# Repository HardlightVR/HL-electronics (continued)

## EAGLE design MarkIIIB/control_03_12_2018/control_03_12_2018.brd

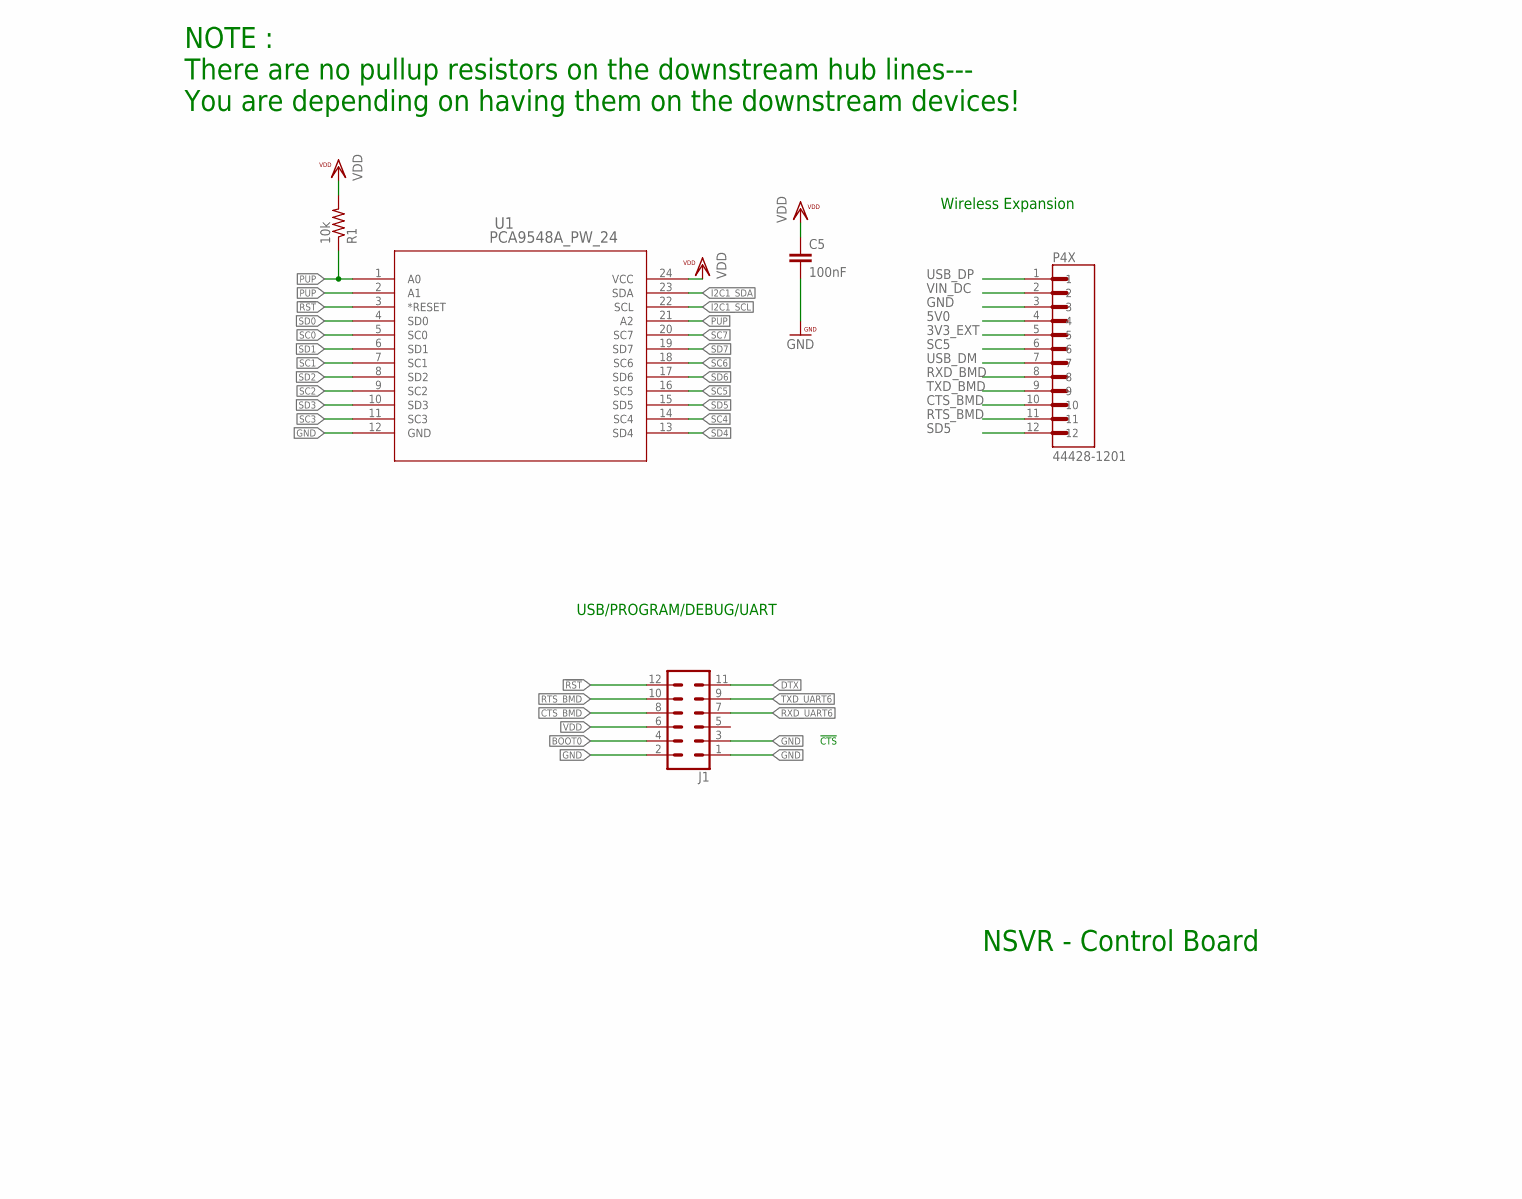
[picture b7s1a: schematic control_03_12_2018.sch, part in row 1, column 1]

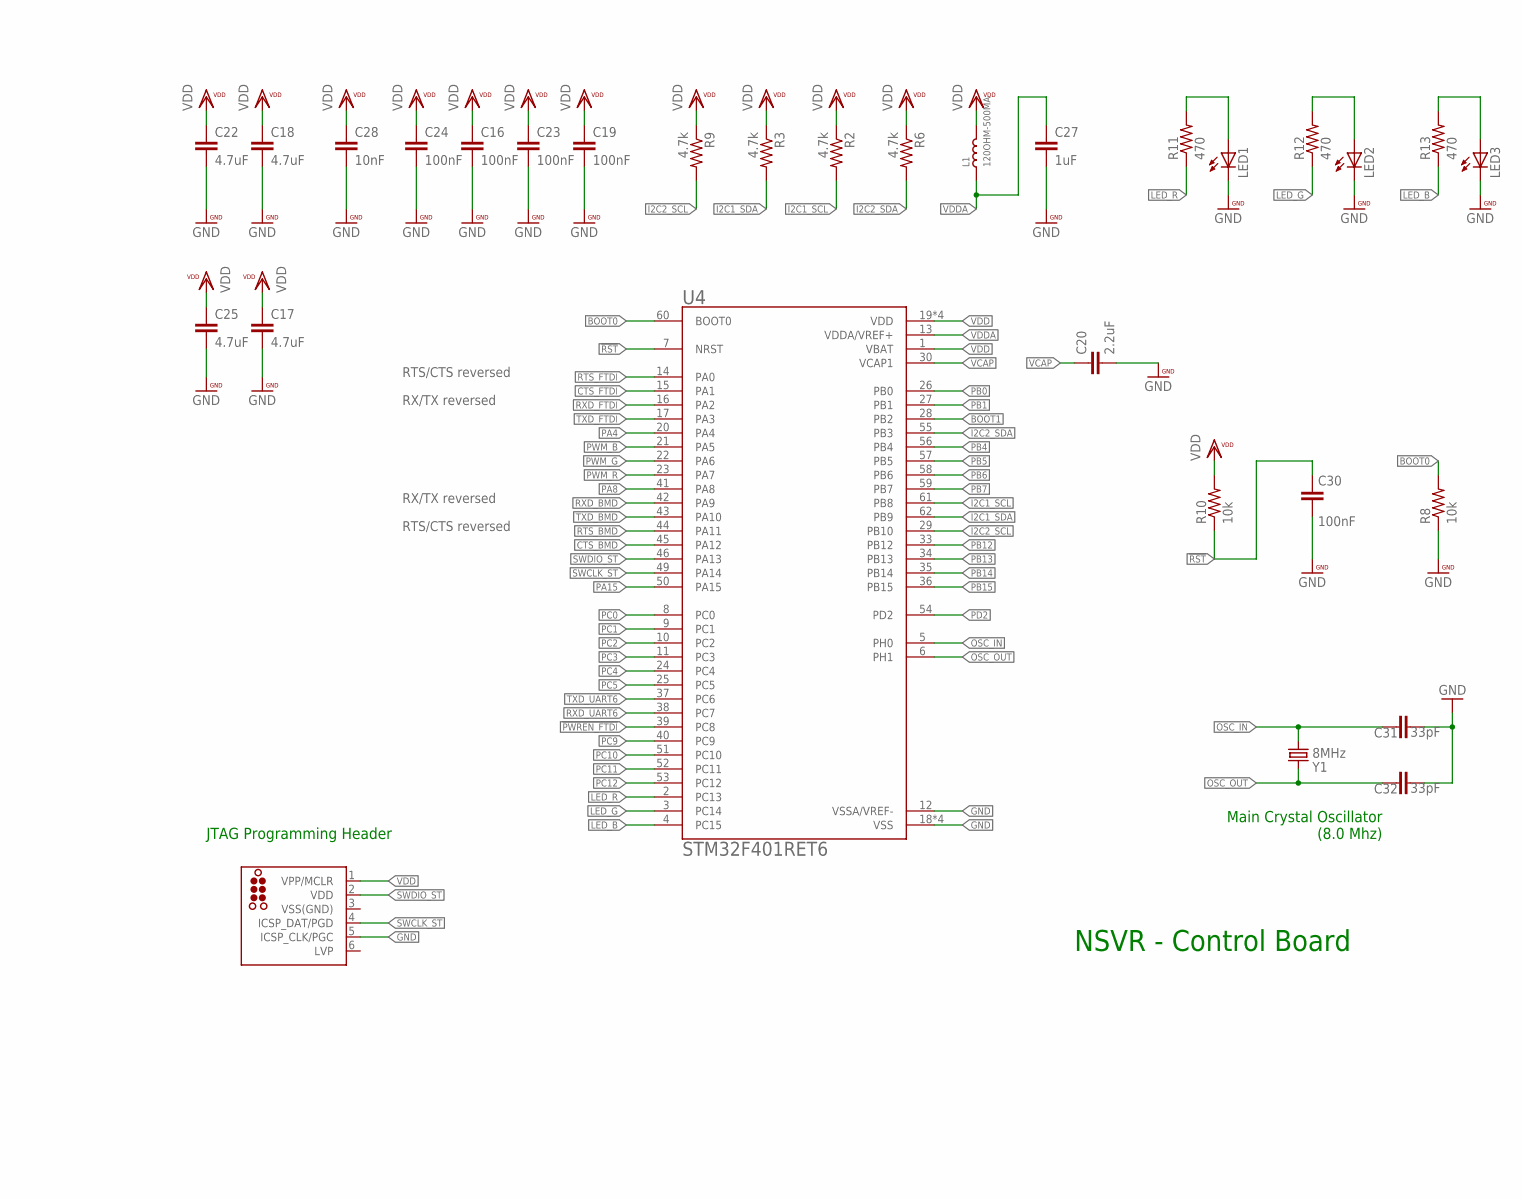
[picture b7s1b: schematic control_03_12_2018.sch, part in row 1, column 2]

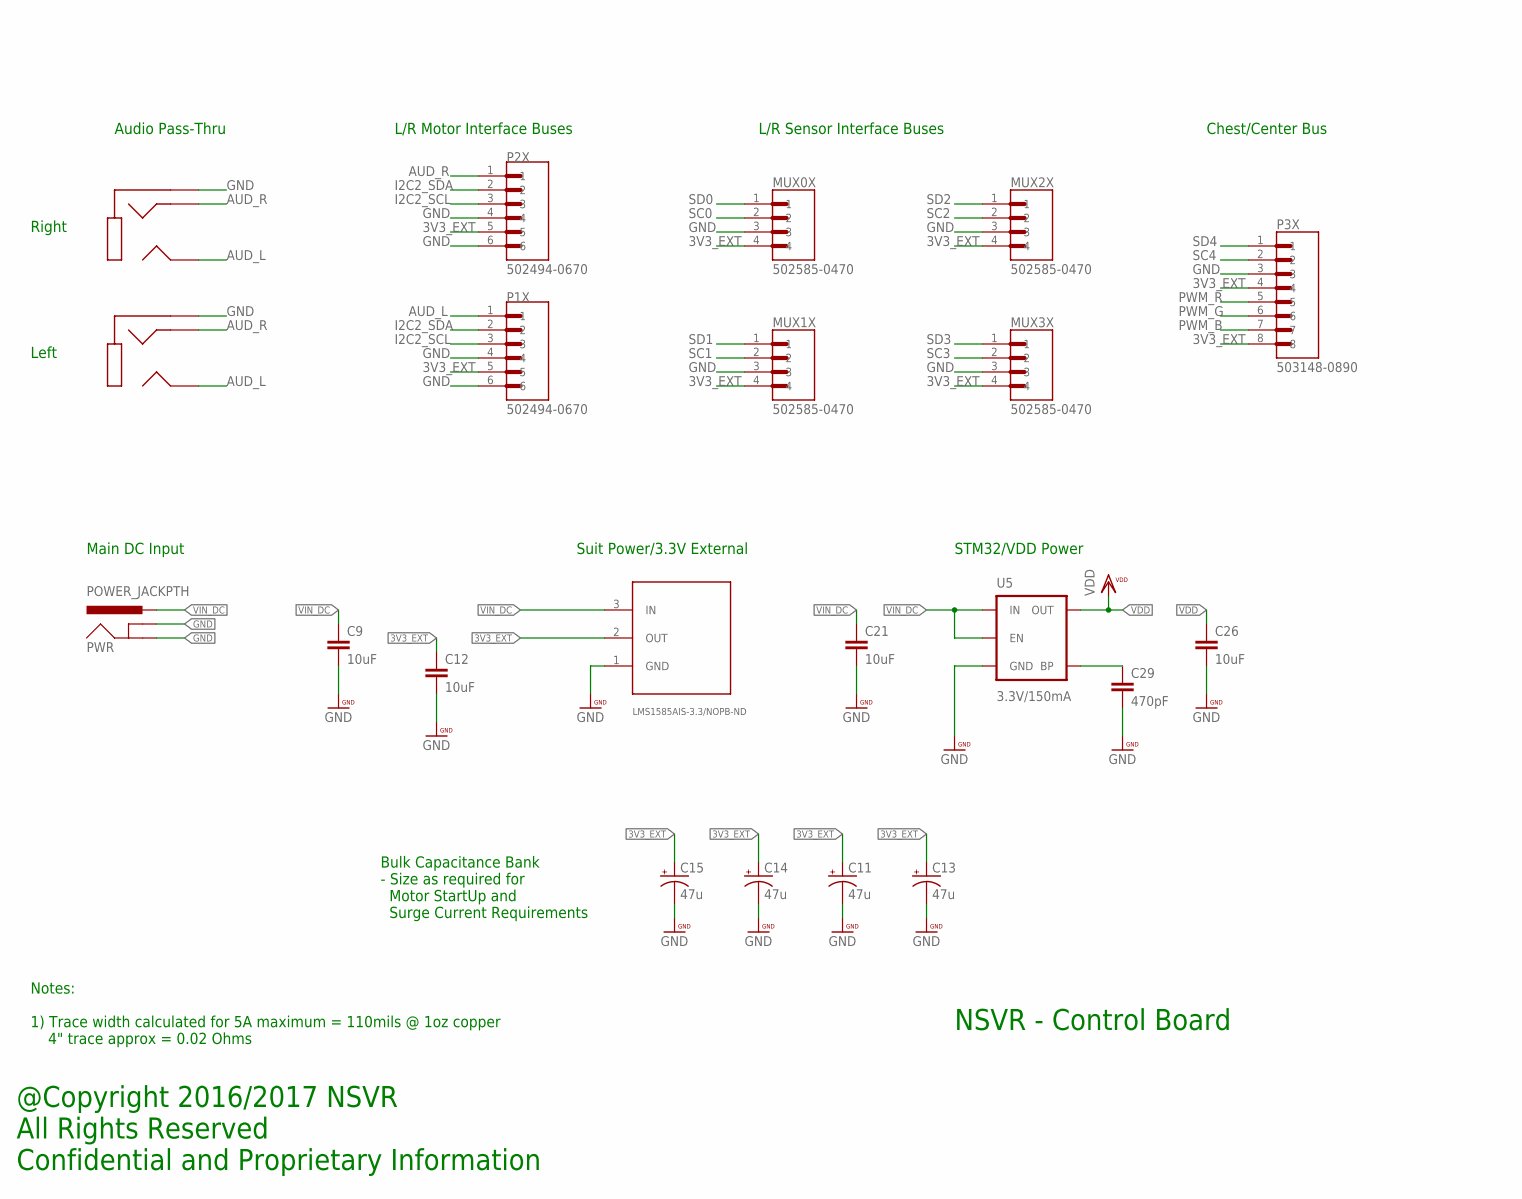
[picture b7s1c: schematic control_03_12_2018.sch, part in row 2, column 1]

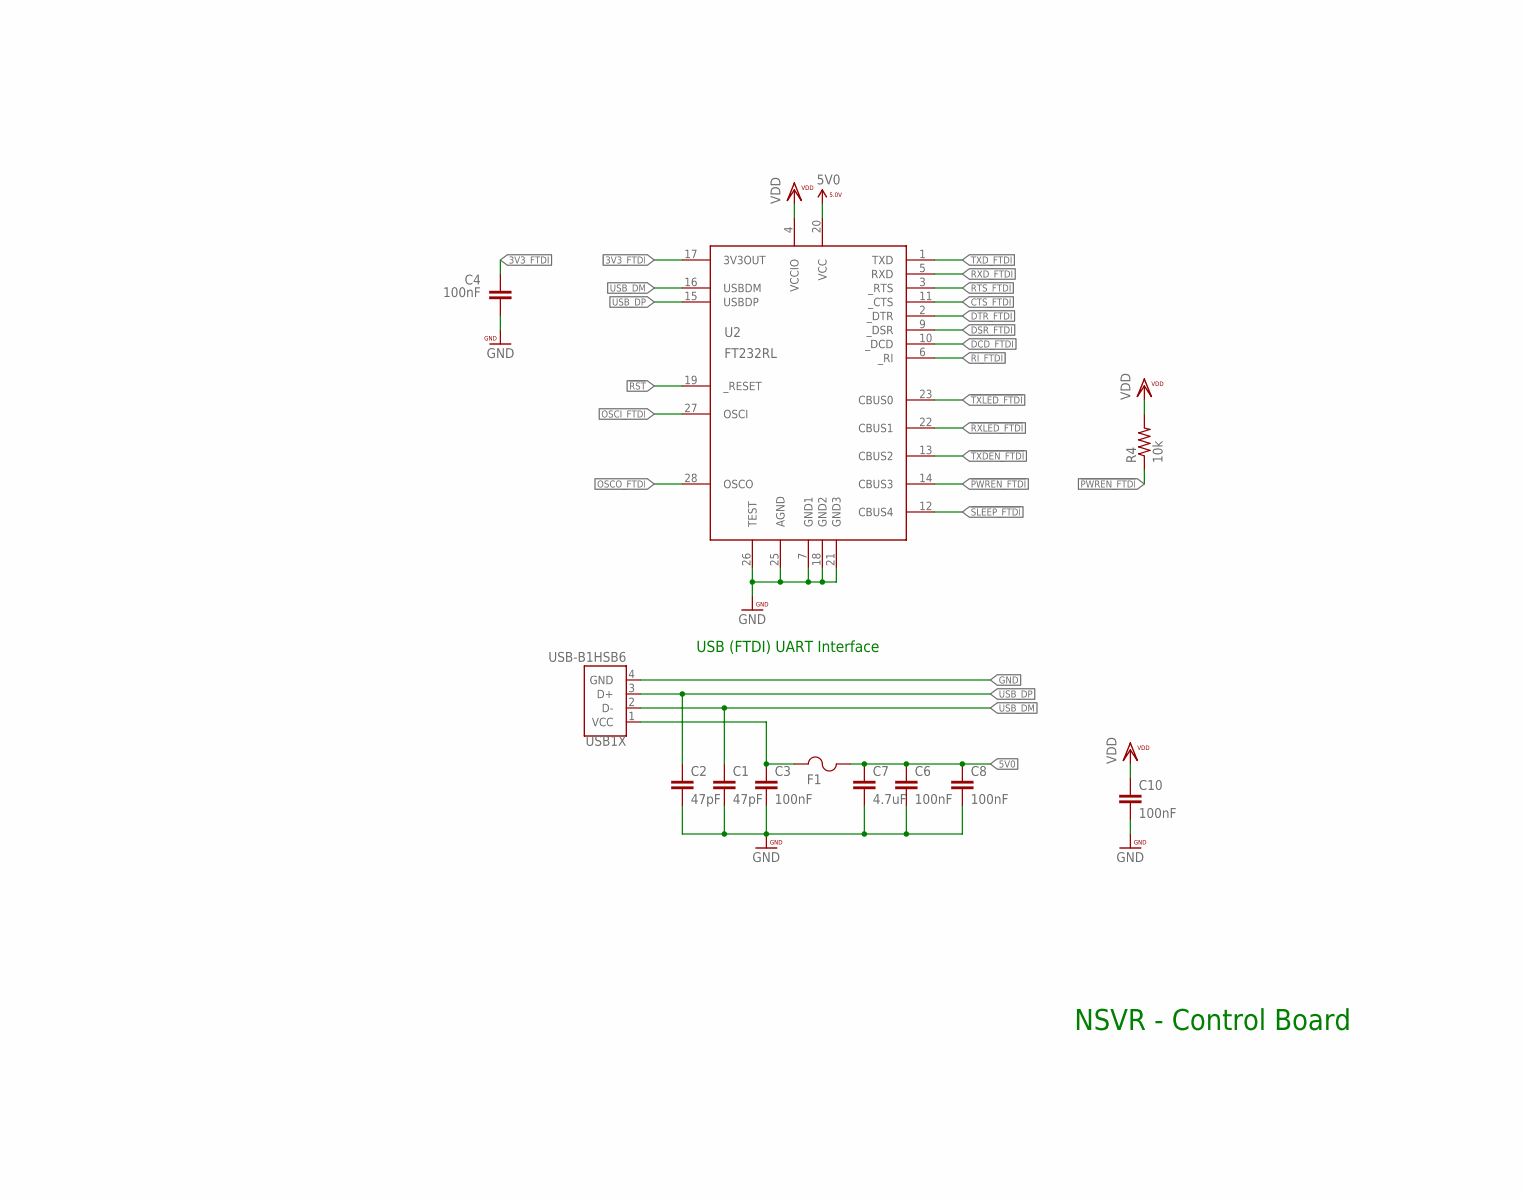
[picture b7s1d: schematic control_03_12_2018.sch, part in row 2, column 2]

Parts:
C1, C2: 47pF; 0402-CAP
C3, C4, C5, C6, C8, C10, C16, C19, C23, C24, C30: 100nF; 0402-CAP
C7, C17, C18, C22, C25: 4.7uF; 0402-CAP
C9, C12, C21, C26: 10uF; 0603-CAP
C11, C13, C14, C15: 47u; PANASONIC_D
C20: 2.2uF; 0402-CAP
C27: 1uF; 0402-CAP
C28: 10nF; 0402-CAP
C29: 470pF; 0402-CAP
C31, C32: 33pF; 0402-CAP
F1: 1206L050YR; 1206LSERIES
J1: CONN_06X2SMD_FEMALE; 2X6_SMD
J_ST: TC2030-MCP-NL
L1: 120OHM-500MA; L0603
LED1, LED2, LED3: LEDCHIP-LED0603; CHIP-LED0603
MUX0X, MUX1X, MUX2X, MUX3X: 502585-0470; MOLEX_502585-0470
P1X, P2X: 502494-0670; MOLEX_502494-0670
P3X: 503148-0890; MOLEX_503148-0890
P4X: 44428-1201; MOLEX_44428-1201
PJ1, PJ2: SJ1-3513N; SJ1-351XN
PWR: POWER_JACKPTH; POWER_JACK_PTH
R1, R4, R8, R10: 10k; EIA-0402
R2, R3, R6, R9: 4.7k; EIA-0402
R11, R12, R13: 470; EIA-0402
U1: PCA9548A_PW_24; PW24
U2: FT232RL; SSOP28DB
U3: LMS1585AIS-3.3/NOPB-ND; TO254P1524X483-4N
U4: STM32F401RET6; QFP50P1200X1200X160-64N
U5: 3.3V/150mA; SOT23-5
USB1X: USB-B1HSB6; OST_USB-B1HSB6
Y1: 8MHz; CRYSTAL-SMD-5X3

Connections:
3V3_EXT: C11.+, C12.1, C13.+, C14.+, C15.+, MUX0X.4, MUX1X.4, MUX2X.4, MUX3X.4, P1X.5, P2X.5, P3X.4, P3X.8, P4X.5, U3.2 (OUT)
3V3_FTDI: C4.1, U2.17 (3V3OUT)
5V0: C6.1, C7.1, C8.1, F1.2, P4X.4, U2.20 (VCC)
!PWREN_FTDI: R4.1, U2.14 (CBUS3), U4.39 (PC8)
!RST: C30.1, J1.12, R10.1, U1.3 (*RESET), U2.19 (_RESET), U4.7 (NRST)
!RXLED_FTDI: U2.22 (CBUS1)
!SLEEP_FTDI: U2.12 (CBUS4)
!TXDEN_FTDI: U2.13 (CBUS2)
!TXLED_FTDI: U2.23 (CBUS0)
AUD_L: P1X.1, PJ1.2, PJ2.2
AUD_R: P2X.1, PJ1.3, PJ2.3
BOOT0: J1.4, R8.2, U4.60 (BOOT0)
BOOT1: U4.28 (PB2)
CTS_BMD: J1.8, P4X.10, U4.45 (PA12)
CTS_FTDI: U2.11 (_CTS), U4.15 (PA1)
DCD_FTDI: U2.10 (_DCD)
DSR_FTDI: U2.9 (_DSR)
DTR_FTDI: U2.2 (_DTR)
DTX: J1.11
GND: C1.2, C2.2, C3.2, C4.2, C5.2, C6.2, C7.2, C8.2, C9.2, C10.2, C11.-, C12.2, C13.-, C14.-, C15.-, C16.2, C17.2, C18.2, C19.2, C20.2, C21.2, C22.2, C23.2, C24.2, C25.2, C26.2, C27.2, C28.2, C29.2, C30.2, C31.1, C32.1, J1.1, J1.2, J1.3, J_ST.5 (ICSP_CLK/PGC), LED1.C, LED2.C, LED3.C, MUX0X.3, MUX1X.3, MUX2X.3, MUX3X.3, P1X.4, P1X.6, P2X.4, P2X.6, P3X.3, P4X.3, PJ1.1, PJ2.1, PWR.GND, PWR.GNDBREAK, R8.1, U1.12 (GND), U2.7 (GND1), U2.18 (GND2), U2.21 (GND3), U2.25 (AGND), U2.26 (TEST), U3.1 (GND), U4.12 (VSSA/VREF-), U4.18 (VSS), U4.31 (VSS), U4.47 (VSS), U4.63 (VSS), U5.2 (GND), USB1X.4 (GND)
I2C1_SCL: R2.2, U1.22 (SCL), U4.61 (PB8)
I2C1_SDA: R3.2, U1.23 (SDA), U4.62 (PB9)
I2C2_SCL: P1X.3, P2X.3, R9.2, U4.29 (PB10)
I2C2_SDA: P1X.2, P2X.2, R6.2, U4.55 (PB3)
LED1: LED1.A, R11.2
LED2: LED2.A, R12.2
LED3: LED3.A, R13.2
LED_B: R13.1, U4.4 (PC15)
LED_G: R12.1, U4.3 (PC14)
LED_R: R11.1, U4.2 (PC13)
unnamed: C29.1, U5.4 (BP)
OSCI_FTDI: U2.27 (OSCI)
OSCO_FTDI: U2.28 (OSCO)
OSC_IN: C31.2, U4.5 (PH0), Y1.1
OSC_OUT: C32.2, U4.6 (PH1), Y1.3 (2)
PA4: U4.20 (PA4)
PA8: U4.41 (PA8)
PA15: U4.50 (PA15)
PB0: U4.26 (PB0)
PB1: U4.27 (PB1)
PB4: U4.56 (PB4)
PB5: U4.57 (PB5)
PB6: U4.58 (PB6)
PB7: U4.59 (PB7)
PB12: U4.33 (PB12)
PB13: U4.34 (PB13)
PB14: U4.35 (PB14)
PB15: U4.36 (PB15)
PC0: U4.8 (PC0)
PC1: U4.9 (PC1)
PC2: U4.10 (PC2)
PC3: U4.11 (PC3)
PC4: U4.24 (PC4)
PC5: U4.25 (PC5)
PC9: U4.40 (PC9)
PC10: U4.51 (PC10)
PC11: U4.52 (PC11)
PC12: U4.53 (PC12)
PD2: U4.54 (PD2)
PUP: R1.1, U1.1 (A0), U1.2 (A1), U1.21 (A2)
PWM_B: P3X.7, U4.21 (PA5)
PWM_G: P3X.6, U4.22 (PA6)
PWM_R: P3X.5, U4.23 (PA7)
RI_FTDI: U2.6 (_RI)
RTS_BMD: J1.10, P4X.11, U4.44 (PA11)
RTS_FTDI: U2.3 (_RTS), U4.14 (PA0)
RXD_BMD: P4X.8, U4.42 (PA9)
RXD_FTDI: U2.5 (RXD), U4.16 (PA2)
RXD_UART6: J1.7, U4.38 (PC7)
SC0: MUX0X.2, U1.5 (SC0)
SC1: MUX1X.2, U1.7 (SC1)
SC2: MUX2X.2, U1.9 (SC2)
SC3: MUX3X.2, U1.11 (SC3)
SC4: P3X.2, U1.14 (SC4)
SC5: P4X.6, U1.16 (SC5)
SC6: U1.18 (SC6)
SC7: U1.20 (SC7)
SD0: MUX0X.1, U1.4 (SD0)
SD1: MUX1X.1, U1.6 (SD1)
SD2: MUX2X.1, U1.8 (SD2)
SD3: MUX3X.1, U1.10 (SD3)
SD4: P3X.1, U1.13 (SD4)
SD5: P4X.12, U1.15 (SD5)
SD6: U1.17 (SD6)
SD7: U1.19 (SD7)
SWCLK_ST: J_ST.4 (ICSP_DAT/PGD), U4.49 (PA14)
SWDIO_ST: J_ST.2 (VDD), U4.46 (PA13)
TXD_BMD: P4X.9, U4.43 (PA10)
TXD_FTDI: U2.1 (TXD), U4.17 (PA3)
TXD_UART6: J1.9, U4.37 (PC6)
USB_DM: C1.1, P4X.7, U2.16 (USBDM), USB1X.2 (D-)
USB_DP: C2.1, P4X.1, U2.15 (USBDP), USB1X.3 (D+)
VBUS_IN: C3.1, F1.1, USB1X.1 (VCC)
VCAP: C20.1, U4.30 (VCAP1)
VDD: C5.1, C10.1, C16.1, C17.1, C18.1, C19.1, C22.1, C23.1, C24.1, C25.1, C26.1, C28.1, J1.6, J_ST.1 (VPP/MCLR), L1.2, R1.2, R2.1, R3.1, R4.2, R6.1, R9.1, R10.2, U1.24 (VCC), U2.4 (VCCIO), U4.1 (VBAT), U4.19 (VDD), U4.32 (VDD), U4.48 (VDD), U4.64 (VDD), U5.5 (OUT)
VDDA: C27.1, L1.1, U4.13 (VDDA/VREF+)
VIN_DC: C9.1, C21.1, P4X.2, PWR.PWR, U3.3 (IN), U5.1 (IN), U5.3 (EN)
VSS(GND): J_ST.3 (VSS(GND))

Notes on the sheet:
RX/TX reversed
RTS/CTS reversed
NSVR - Control Board
@Copyright 2016/2017 NSVR All Rights Reserved Confidential and Proprietary Information
Main Crystal Oscillator (8.0 Mhz)
JTAG Programming Header
USB (FTDI) UART Interface
STM32/VDD Power
Audio Pass-Thru
Wireless Expansion
L/R Motor Interface Buses
Right
Left
Chest/Center Bus
L/R Sensor Interface Buses
Bulk Capacitance Bank - Size as required for Motor StartUp and Surge Current Requirements
Notes: 1) Trace width calculated for 5A maximum = 110mils @ 1oz copper 4" trace approx = 0.02 Ohms
Suit Power/3.3V External
Main DC Input
NOTE : There are no pullup resistors on the downstream hub lines--- You are depending on having them on the downstream devices!
USB/PROGRAM/DEBUG/UART
!CTS

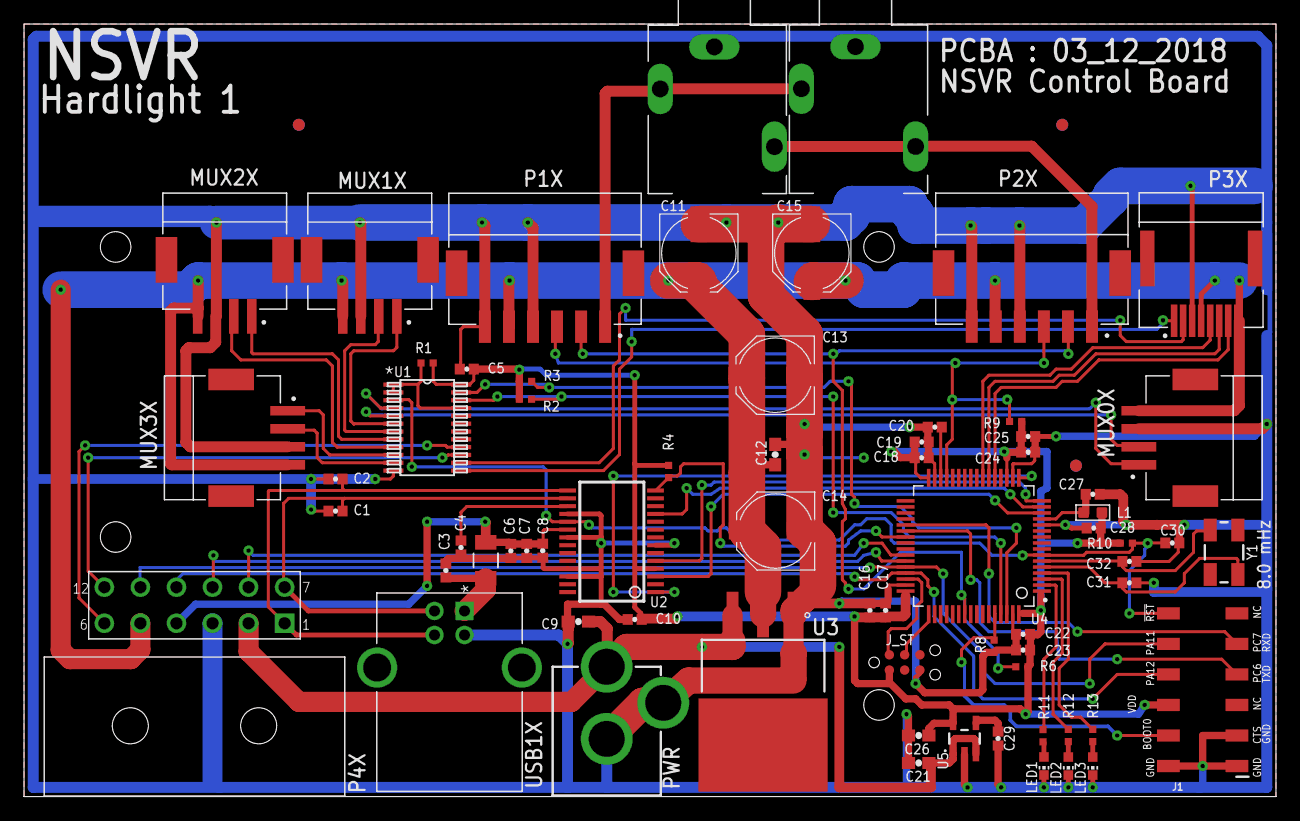
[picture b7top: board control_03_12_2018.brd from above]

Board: 2 copper layers, 104.1 x 64.3 mm, 72 parts (1 on the bottom side), 57 nets.

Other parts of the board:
U$1, U$2, U$3: CIRCLE-1MM-3R
U$100: NSVR_LOGO

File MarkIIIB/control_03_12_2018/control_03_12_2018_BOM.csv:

Qty,Value,Device,Package,Parts,Description
1,,CONN_06X2SMD_FEMALE,2X6_SMD,J1,Multi connection point. Often used as Generic Header-pin footprint for 0.1 inch spaced/style header connections
3,,LEDCHIP-LED0603,CHIP-LED0603,"LED1, LED2, LED3",LED
1,,TC2030-MCP-NL,TC2030-MCP-NL,J_ST,TAG-CONNECT ICSP ConnectorManufacturer: Tag-Connect
11,100nF,CAP0402-CAP,0402-CAP,"C3, C4, C5, C6, C8, C10, C16, C19, C23, C24, C30",Capacitor
4,10k,RESISTOR0402-TYP,EIA-0402,"R1, R4, R8, R10",Resistor
1,10nF,CAP0402-CAP,0402-CAP,C28,Capacitor
4,10uF,CAP0603-CAP,0603-CAP,"C9, C12, C21, C26",Capacitor
1,1206L050YR,1206L050YR,1206LSERIES,F1,
1,120OHM-500MA,SMD-FERRITE-CHIP-120-OHM-500MA(0603),L0603,L1,303030001
1,1uF,CAP0402-CAP,0402-CAP,C27,Capacitor
1,2.2uF,CAP0402-CAP,0402-CAP,C20,Capacitor
1,3.3V/150mA,V_REG_MIC52053.3V,SOT23-5,U5,"V_REG MIC5205 Standard 3.3V, 5V, and Adjustable 150mA LDO voltage regulator in SOT-23 layout. Micrel part MIC5205. BP (by-pass) pin is used to lower output noise with 470pF cap, may be left open. On the adjustable version BP is used to set output."
2,33pF,CAP0402-CAP,0402-CAP,"C31, C32",Capacitor
4,4.7k,RESISTOR0402-TYP,EIA-0402,"R2, R3, R6, R9",Resistor
5,4.7uF,CAP0402-CAP,0402-CAP,"C7, C17, C18, C22, C25",Capacitor
1,44428-1201,44428-1201,MOLEX_44428-1201,P4X,Conn Wire to Board HDR 12 POS 3mm Solder RA Thru-Hole Micro-Fit 3.0 BMI? Tray
3,470,RESISTOR0402-TYP,EIA-0402,"R11, R12, R13",Resistor
1,470pF,CAP0402-CAP,0402-CAP,C29,Capacitor
2,47pF,CAP0402-CAP,0402-CAP,"C1, C2",Capacitor
4,47u,CAP_POLD,PANASONIC_D,"C11, C13, C14, C15",Capacitor Polarized
2,502494-0670,502494-0670,MOLEX_502494-0670,"P1X, P2X","2.00mm Pitch CLIK-Mateﾙ Wire-to-Board PCB Receptacle, Single Row, Right Angle, 6 Circuits"
4,502585-0470,502585-0470,MOLEX_502585-0470,"MUX0X, MUX1X, MUX2X, MUX3X","1.50mm Pitch CLIK-Mateﾙ Wire-to-Board PCB Receptacle, Single Row, Right Angle, 4 Circuits"
1,503148-0890,503148-0890,MOLEX_503148-0890,P3X,1.5wb Dual r/a Embs Tape Pkg 8p
1,8MHz,CRYSTAL5X3,CRYSTAL-SMD-5X3,Y1,Crystals
1,FT232RL,FT232RL,SSOP28DB,U2,USB UART
1,LMS1585AIS-3.3/NOPB-ND,LMS1585AIS-3.3/NOPB-ND,TO254P1524X483-4N,U3,
1,PCA9548A_PW_24,PCA9548A_PW_24,PW24,U1,
1,POWER_JACKPTH,POWER_JACKPTH,POWER_JACK_PTH,PWR,Power Jack
2,SJ1-3513N,SJ1-3513N,SJ1-351XN,"PJ1, PJ2",
1,STM32F401RET6,STM32F401RET6,QFP50P1200X1200X160-64N,U4,MCU 32-Bit STM32 ARM Cortex M4 RISC 512KB Flash 1.8V/2.5V/3.3V 64-Pin LQFP Tray
1,USB-B1HSB6,USB-B1HSB6,OST_USB-B1HSB6,USB1X,Conn Usb Type b r/a Black

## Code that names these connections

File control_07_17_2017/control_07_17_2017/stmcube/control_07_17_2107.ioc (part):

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Mcu.Name=STM32F401R(D-E)Tx
Mcu.Package=LQFP64
Mcu.UserName=STM32F401RETx
PA0-WKUP.Mode=CTS_RTS
PA0-WKUP.Signal=USART2_CTS
PA1.Mode=CTS_RTS
PA1.Signal=USART2_RTS
PA10.Mode=Asynchronous
PA10.Signal=USART1_RX
PA11.Mode=CTS_RTS
PA11.Signal=USART1_CTS
PA12.Mode=CTS_RTS
PA12.Signal=USART1_RTS
PA13.Mode=Serial_Wire
PA13.Signal=SYS_JTMS-SWDIO
PA14.Mode=Serial_Wire
PA14.Signal=SYS_JTCK-SWCLK
PA2.Mode=Asynchronous
PA2.Signal=USART2_TX
PA3.Mode=Asynchronous
PA3.Signal=USART2_RX
PA5.Signal=GPIO_Output
PA6.Signal=GPIO_Output
PA7.Signal=GPIO_Output
PA9.Mode=Asynchronous
PA9.Signal=USART1_TX
PB10.Mode=I2C
PB10.Signal=I2C2_SCL
PB3.Mode=I2C
PB3.Signal=I2C2_SDA
PB8.Mode=I2C
PB8.Signal=I2C1_SCL
PB9.Mode=I2C
PB9.Signal=I2C1_SDA
PC13-ANTI_TAMP.Signal=GPIO_Output
PC14-OSC32_IN.Signal=GPIO_Output
PC15-OSC32_OUT.Signal=GPIO_Output
PC2.Signal=ADCx_IN12
PC3.Signal=ADCx_IN13
PC6.Mode=Asynchronous
PC6.Signal=USART6_TX
PC7.Mode=Asynchronous
PC7.Signal=USART6_RX
PC8.Signal=GPIO_Input
PH0\ -\ OSC_IN.Mode=HSE-External-Oscillator
PH0\ -\ OSC_IN.Signal=RCC_OSC_IN
PH1\ -\ OSC_OUT.Mode=HSE-External-Oscillator
PH1\ -\ OSC_OUT.Signal=RCC_OSC_OUT
RCC.HSE_VALUE=8000000
RCC.SYSCLKFreq_VALUE=16000000

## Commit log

2017-08-03 InitialCheckIn
    07/22/2017
2017-08-03 Add README
2017-09-27 Add Battery & BTLE boards
2017-10-01 combo IMU & Chest
2017-10-13 Add BTLE config docs
2017-10-13 try png format
2017-10-13 try gif format
2017-10-20 Add Battery & Mounting Holes to BLTE board
2017-11-24 Add MarkIIIB Heirarchy
2017-12-22 Add WiFi Boards
2018-01-01 Wi-Fi Suit Firmware test version
2018-01-12 SOW7 - Control Board & WiFi boards delivery
2018-01-15 update wifi-firmware
2018-01-15 NSVR_Telnet working version
2018-01-16 add Control Programming Board
2018-01-16 add Telnet
2018-01-25 Revise WiFi Board to increase Case Clearance
2018-02-02 Potential fix to latency issue with wifi firmware
2018-02-17 Fix RTS so Wireless board can communicate with suit
2018-02-18 add RTS handshaking
2018-03-09 update telnet
2018-03-13 03_12_2018 Update
2018-03-15 Notch Wifi board for case clearances
2018-03-23 add new Wi-Fi boards to inventory.txt
2018-03-29 Add Centroid Files for CM
2018-04-02 Resistor Footprint update
2018-04-04 Add Part Number ROllup Spreadsheets
2019-01-10 cleanup for open release
2019-01-10 readme cleanup
2019-01-10 Create LICENSE
